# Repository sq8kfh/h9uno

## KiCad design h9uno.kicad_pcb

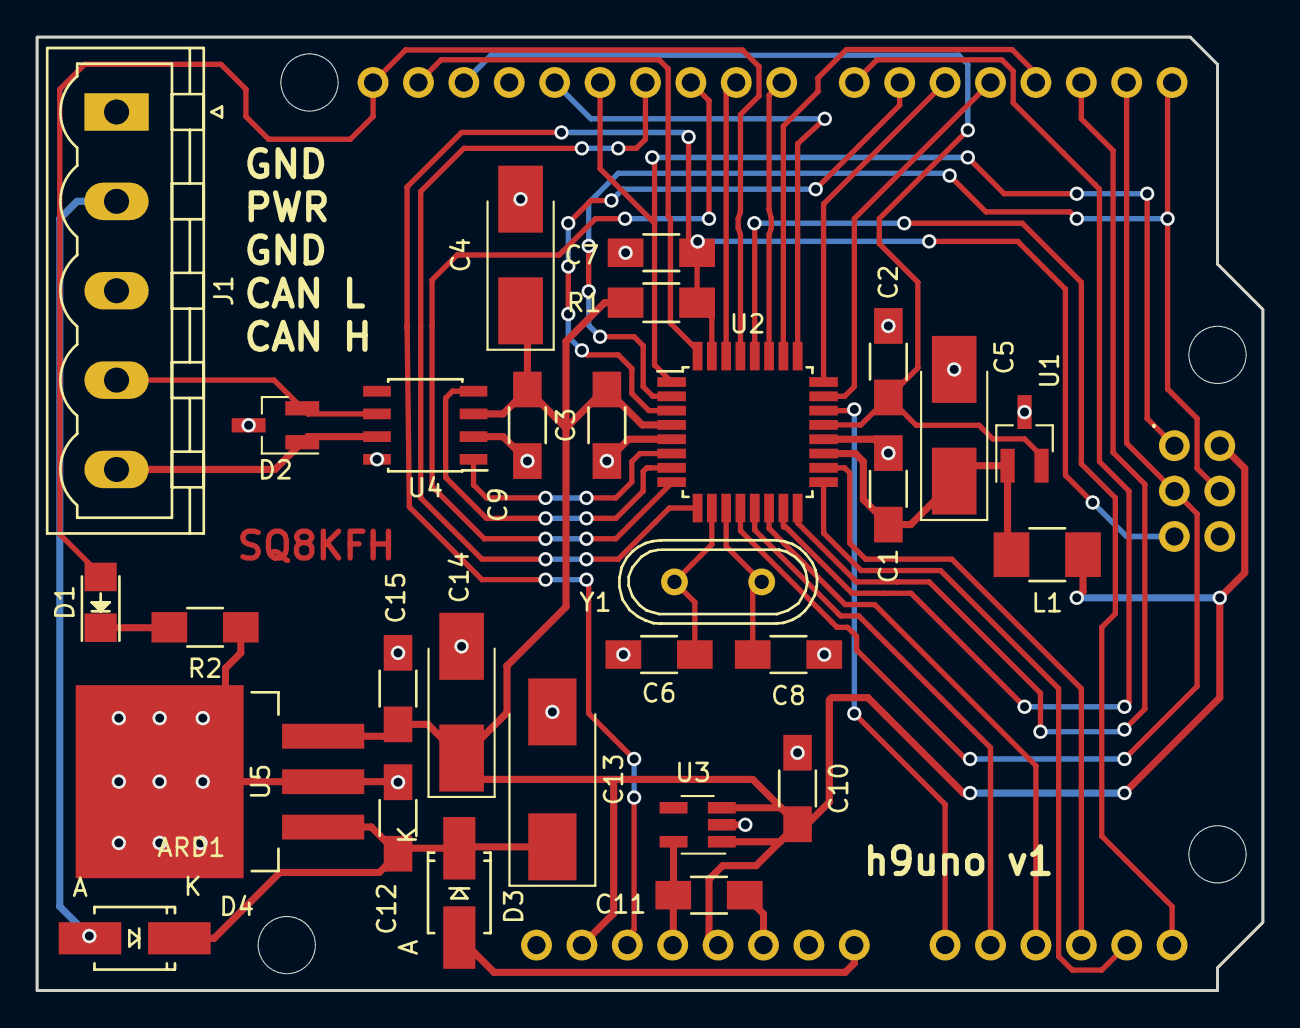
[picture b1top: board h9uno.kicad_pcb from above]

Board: 2 copper layers, 68.6 x 53.3 mm, 30 parts (0 on the bottom side), 38 nets.

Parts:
ARD1: Arduino_Uno_Shield
C1, C3, C9, C12, C15: 100n; C_1206_HandSoldering
C2, C10, C11: 1u; C_1206_HandSoldering
C4, C5: 47u; CP_Tantalum_Case-C_EIA-6032-28_Hand
C6, C8: 22p; C_1206_HandSoldering
C7: 4n7; C_1206_HandSoldering
C13: 100u; CP_Tantalum_Case-D_EIA-7343-31_Hand
C14: 100u; CP_Tantalum_Case-C_EIA-6032-28_Hand
D1: LED_ALT; LED_1206
D2: NUP2105; SOT-23_Handsoldering
D3, D4: S1A; SMA_Handsoldering
J1: CAN; PhoenixContact_MSTBVA-G_05x5.00mm_Vertical
L1: 10uH; R_1210_HandSoldering
R1: 10k; R_1206_HandSoldering
R2: 1k; R_1206_HandSoldering
U1: MCP1525; SOT-23_Handsoldering
U2: ATMEGA32M1-AU; TQFP-32_7x7mm_Pitch0.8mm
U3: LP2985LV; SOT-23-5_HandSoldering
U4: MCP2551-I/SN; SOIC-8_3.9x4.9mm_Pitch1.27mm
U5: LM7805CT; TO-263-3Lead
Y1: 16MHz; Crystal_HC49-U_Vertical

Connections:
+3V3: ARD1.3.3V, C11.2, U3.5
+5V: ARD1.5V1, ARD1.5V2, ARD1.IORF, C3.2, C4.1, C9.2, C10.2, C14.1, C15.1, L1.1, R1.2, U2.4, U3.1, U3.3, U4.3, U5.3
+5VA: C1.2, C5.1, L1.2, U1.1, U2.19
/A0: ARD1.A0, U2.22
/A1: ARD1.A1, U2.13
/A2: ARD1.A2, U2.14
/A3: ARD1.A3, U2.18
/A4: ARD1.A4, U2.17
/A5: ARD1.A5, U2.28
/AREF: ARD1.AREF, C2.2, U1.2, U2.21
/CAN_RX: U2.7, U4.4
/CAN_TX: U2.6, U4.1
/D2_INT: ARD1.D2, U2.16
/D3_INT: ARD1.D3, U2.26
/D4: ARD1.D4, U2.23
/D5: ARD1.D5, U2.24
/D6: ARD1.D6, U2.3
/D7: ARD1.D7, U2.15
/D8: ARD1.D8, U2.27
/D9: ARD1.D9, U2.30
/D10: ARD1.D10, U2.8
/D11: ARD1.D11, U2.9
/D13: ARD1.D13, U2.25
/MISO: ARD1.D12, ARD1.MISO, U2.1
/MOSI: ARD1.D0, ARD1.MOSI, U2.2
/PD0: ARD1.SCL, D1.2, U2.29
/PD1: ARD1.SDA, U2.32
/RESET: ARD1.RST1, ARD1.RST2, C7.2, R1.1, U2.31
/SCK: ARD1.D1, ARD1.SCK, U2.12
/VIN: ARD1.VIN, D3.2
GND: ARD1.GND1, ARD1.GND2, ARD1.GND3, ARD1.GND4, C1.1, C2.1, C3.1, C4.2, C5.2, C6.1, C7.1, C8.1, C9.1, C10.1, C11.1, C12.2, C13.2, C14.2, C15.2, D2.3, J1.1, J1.3, R2.1, U1.3, U2.5, U2.20, U3.2, U4.2, U4.8, U5.2
unnamed: C6.2, U2.10, Y1.1
unnamed: C8.2, U2.11, Y1.2
unnamed: C12.1, C13.1, D3.1, D4.1, U5.1
unnamed: D1.1, R2.2
unnamed: D2.1, J1.5, U4.7
unnamed: D2.2, J1.4, U4.6
unnamed: D4.2, J1.2

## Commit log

2019-04-22 init
2019-04-22 added rduino-kicad-library 1.4.1
2019-04-22 switch lib to local submodule
2019-04-22 release v1
